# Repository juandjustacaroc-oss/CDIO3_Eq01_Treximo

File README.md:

# CDIO3_Eq01_Treximo: Smart Athletic Timing & Physiological Monitoring System
Sistema distribuido basado en ESP32 para cronometraje automático y monitoreo fisiológico en pruebas de atletismo (100 m), diseñado para proporcionar mediciones precisas de tiempo, velocidad y frecuencia cardíaca en tiempo real. Este proyecto integra comunicación inalámbrica de baja latencia, procesamiento embebido y una interfaz web ligera para ofrecer retroalimentación inmediata al entrenador sin depender de infraestructura externa o servicios en la nube.

# Objetivo del Proyecto
Desarrollar un sistema portátil y autónomo capaz de:
- Detectar automáticamente el inicio y finalización de la carrera.
- Calcular el tiempo exacto del recorrido.
- Estimar la velocidad promedio del atleta.
- Monitorear la frecuencia cardíaca durante la carrera y la fase de recuperación.
- Visualizar métricas en pantalla OLED y en una interfaz web básica embebida.
- Reiniciar el sistema de forma segura para múltiples sesiones consecutivas.

# Arquitectura General
- Peon Salida/Peon Llegada.
- Cerebro Cronometro.
- Banda de variables fisiologicas.
La comunicación entre nodos se realiza mediante ESP-NOW.
El nodo central también opera como punto de acceso WiFi para permitir la visualización de datos desde un smartphone o tablet.

# Estado Actual [MAHD](https://docs.google.com/spreadsheets/d/1o7weHOlPSlPQWPbzmIAxRxXA6ihxt1Q-x_elVm5SotQ/edit?usp=sharing) 
- ✅Hardware funcional
- ✅Comunicación estable entre nodos
- ✅Cronometría precisa basada en eventos
- ❌Monitoreo cardíaco integrado
- ✅Interfaz TFT operativa
- ✅Dashboard web ligero en pruebas

# Librerías necesarias

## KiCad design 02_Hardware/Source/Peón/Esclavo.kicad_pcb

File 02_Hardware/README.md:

# Hardware

## Diseño y Arquitectura Física del Sistema

Esta carpeta contiene todos los recursos asociados al desarrollo físico y electrónico del sistema distribuido basado en ESP32.

El hardware está dividido en tres subsistemas principales:

- 🧠 Cronómetro Central
- 📡 Peones (Salida y Llegada)
- ❤️ Banda de Variables Fisiológicas

---

## Estructura de Carpetas

### 📂 Datasheets/
Contiene únicamente hojas técnicas oficiales (PDF) de los componentes utilizados:
- ESP32
- UWB (DW1000 / RYUW122)
- MAX3010x
- RTC
- Pantalla TFT
- Módulos de carga
- Sensores ultrasónicos

Estos documentos fundamentan las decisiones técnicas adoptadas en el diseño.

---

### 📂 Mechanical/
Archivos mecánicos del proyecto:
- STL (impresión 3D)
- DXF (corte láser)
- CAD (modelos completos)

Incluye:
- Carcasa del cronómetro
- Soportes de peones
- Integración de banda fisiológica

---

### 📂 Source/
Archivos editables de diseño electrónico:
- KiCad
- Altium
- Eagle

Contiene:
- Esquemáticos
- PCB
- Layout
- Gerbers (si aplica)

---

## Consideraciones Técnicas

- Alimentación autónoma con sistema de carga y protección.
- Comunicación inalámbrica UWB para medición de distancia.
- ESP-NOW para eventos críticos de cronometraje.
- Diseño modular para mantenimiento y escalabilidad.

---

## Estado

El hardware ha sido auditado y actualizado tras la revisión técnica del diseño inicial.
Las modificaciones están justificadas en la Matriz de Defensa de Diseño (ver carpeta 01_Gestion).

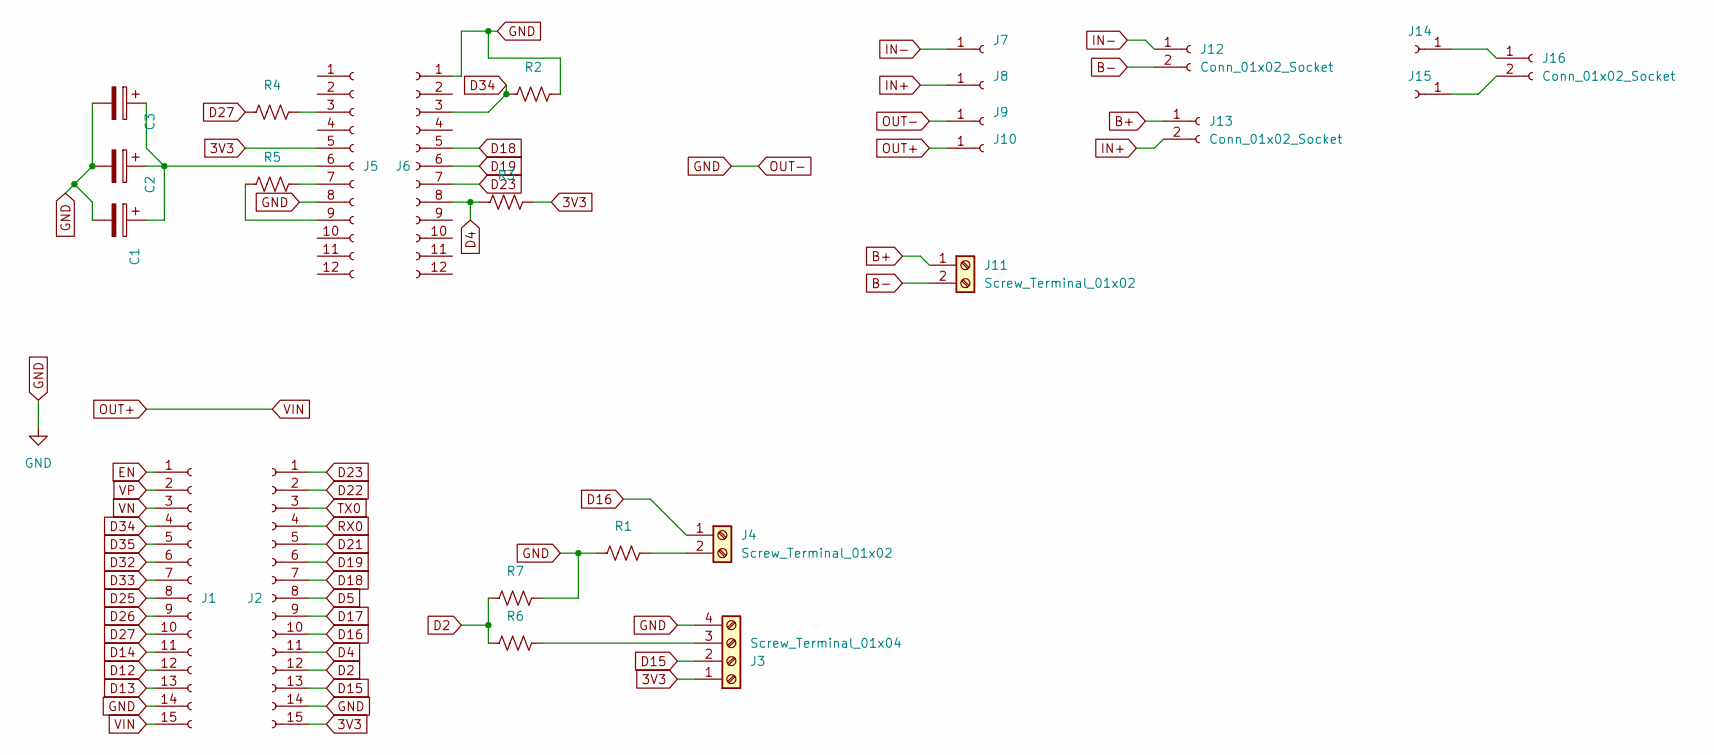
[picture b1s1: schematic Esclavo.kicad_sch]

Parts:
C1, C2, C3: C_Polarized; CP_Radial_D5.0mm_P2.50mm
J1, J2: Conn_01x15_Socket; PinSocket_1x15_P2.54mm_Vertical
J3: Screw_Terminal_01x04; TerminalBlock_Phoenix_MKDS-1,5-4-5.08_1x04_P5.08mm_Horizont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
J4, J11: Screw_Terminal_01x02; TerminalBlock_Phoenix_MKDS-1,5-2-5.08_1x02_P5.08mm_Horizont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
J5, J6: Conn_01x12_Socket; PinSocket_1x12_P2.54mm_Vertical
J7, J8, J9, J10, J14, J15: Conn_01x01_Socket; PinHeader_1x01_P2.54mm_Vertical
J12, J13, J16: Conn_01x02_Socket; PinSocket_1x02_P2.54mm_Vertical
R1, R2, R3, R4, R5, R6, R7: R_US; R_Axial_DIN0207_L6.3mm_D2.5mm_P10.16mm_Horizontal

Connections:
3V3: J2.15, J3.1, J5.5, R3.1
B+: J11.1, J13.1
B-: J11.2, J12.2
D2: J2.12, R6.2, R7.2
D4: J2.11, J6.8, R3.2
D5: J2.8
D12: J1.12
D13: J1.13
D14: J1.11
D15: J2.13, J3.2
D16: J2.10, J4.1
D17: J2.9
D18: J2.7, J6.5
D19: J2.6, J6.6
D21: J2.5
D22: J2.2
D23: J2.1, J6.7
D25: J1.8
D26: J1.9
D27: J1.10, R4.2
D32: J1.6
D33: J1.7
D34: J1.4, J6.3, R2.2
D35: J1.5
EN: J1.1
GND: C1.2, C2.2, C3.2, J1.14, J2.14, J3.4, J5.8, J6.1, J9.1 (Pin_1_1), R1.2, R2.1, R7.1
IN+: J8.1 (Pin_1_1), J13.2
IN-: J7.1 (Pin_1_1), J12.1
unnamed: J3.3, R6.1
unnamed: J4.2, R1.1
unnamed: J5.3, R4.1
unnamed: C1.1, C2.1, C3.1, J5.6
unnamed: J5.7, R5.1
unnamed: J5.9, R5.2
unnamed: J14.1 (Pin_1_1), J16.1
unnamed: J15.1 (Pin_1_1), J16.2
OUT+: J1.15, J10.1 (Pin_1_1)
RX0: J2.4
TX0: J2.3
VN: J1.3
VP: J1.2

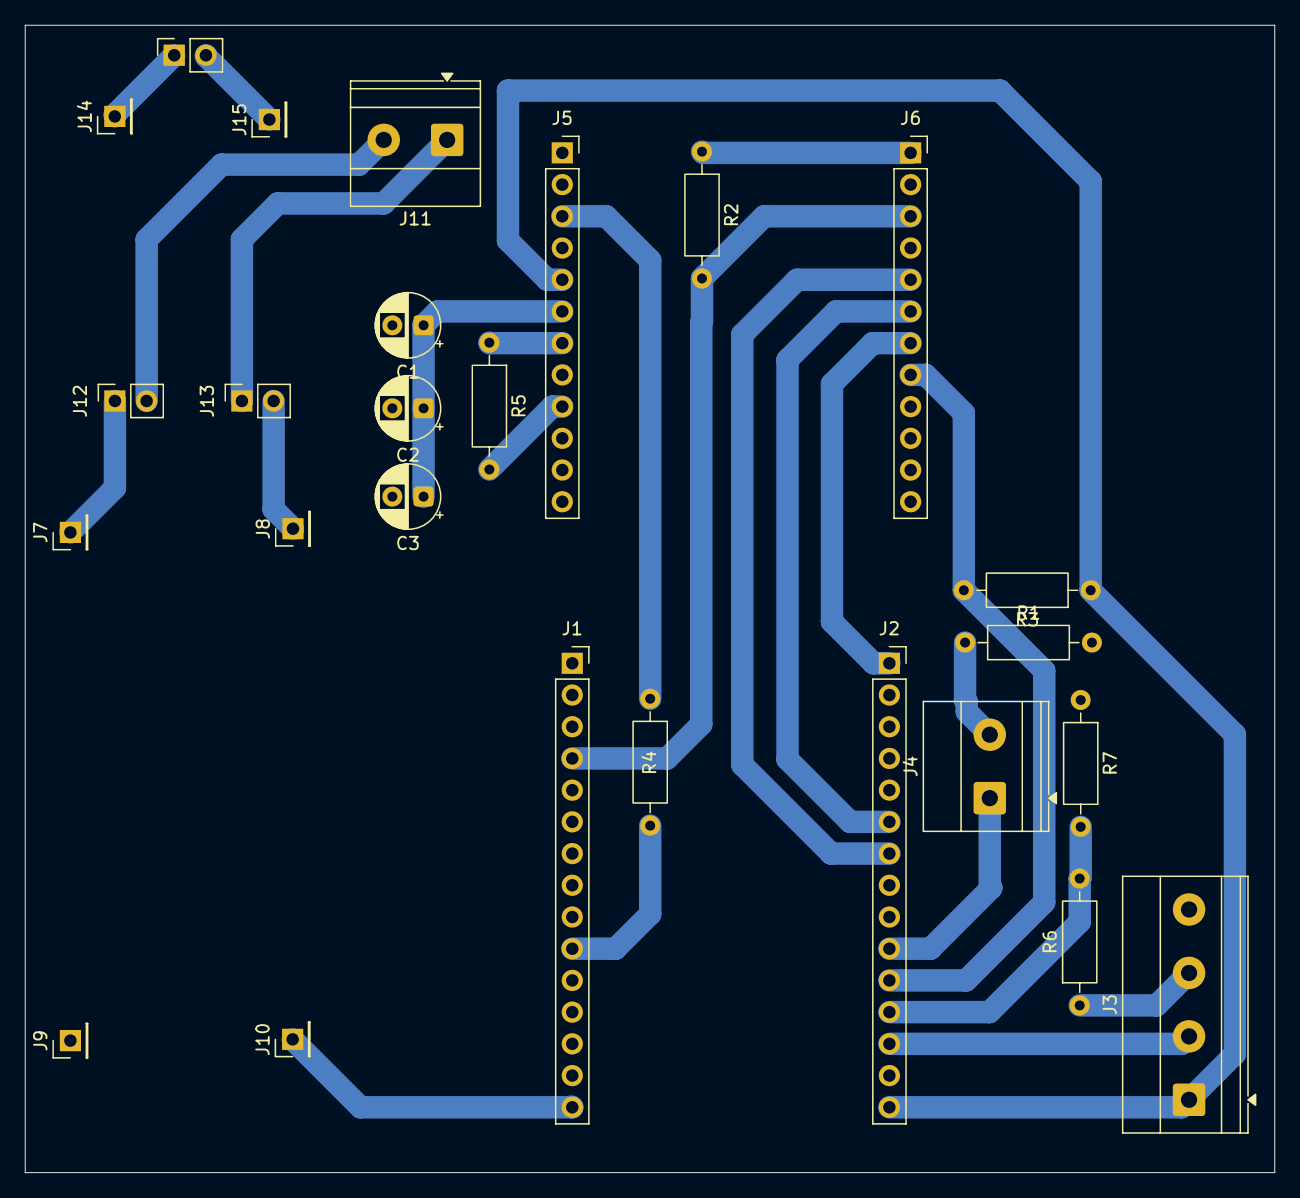
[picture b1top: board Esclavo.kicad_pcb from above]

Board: 2 copper layers, 100.1 x 91.9 mm, 26 parts (0 on the bottom side), 24 nets.

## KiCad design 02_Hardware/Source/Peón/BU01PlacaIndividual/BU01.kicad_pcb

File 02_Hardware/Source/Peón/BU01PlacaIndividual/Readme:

PCB de BU01 para conexión como modulo adicional

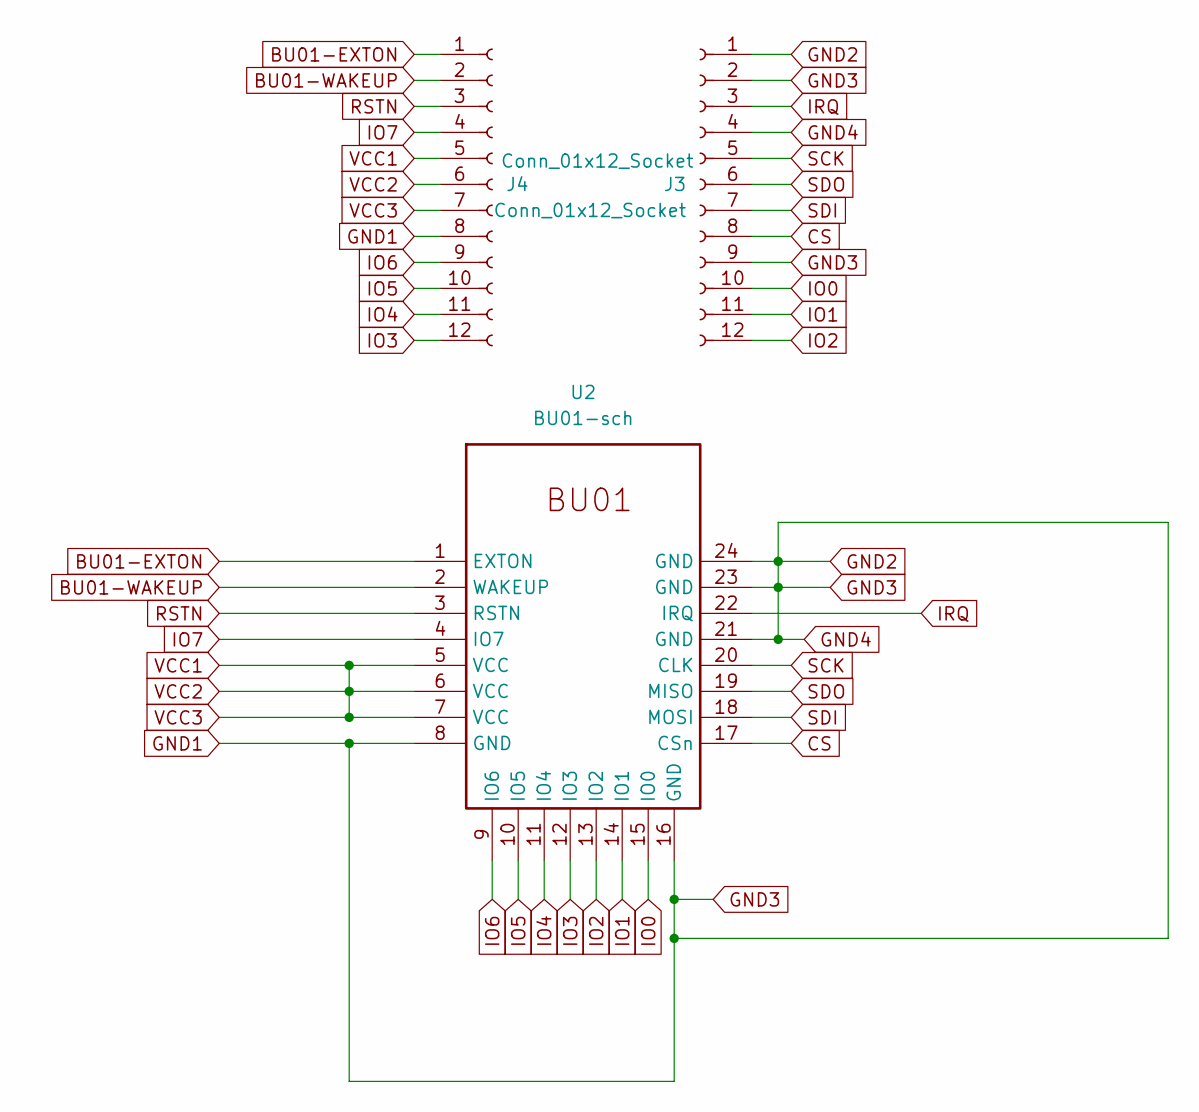
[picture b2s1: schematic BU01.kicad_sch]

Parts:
J3, J4: Conn_01x12_Socket; PinSocket_1x12_P2.54mm_Vertical
U2: BU01-sch; BU01

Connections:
BU01-EXTON: J4.1, U2.1 (EXTON)
BU01-WAKEUP: J4.2, U2.2 (WAKEUP)
CS: J3.8, U2.17 (CSn)
GND1: J3.1, J3.2, J3.4, J3.9, J4.8, U2.8 (GND), U2.16 (GND), U2.21 (GND), U2.23 (GND), U2.24 (GND)
IO0: J3.10, U2.15 (IO0)
IO1: J3.11, U2.14 (IO1)
IO2: J3.12, U2.13 (IO2)
IO3: J4.12, U2.12 (IO3)
IO4: J4.11, U2.11 (IO4)
IO5: J4.10, U2.10 (IO5)
IO6: J4.9, U2.9 (IO6)
IO7: J4.4, U2.4 (IO7)
IRQ: J3.3, U2.22 (IRQ)
RSTN: J4.3, U2.3 (RSTN)
SCK: J3.5, U2.20 (CLK)
SDI: J3.7, U2.18 (MOSI)
SDO: J3.6, U2.19 (MISO)
VCC1: J4.5, J4.6, J4.7, U2.5 (VCC), U2.6 (VCC), U2.7 (VCC)

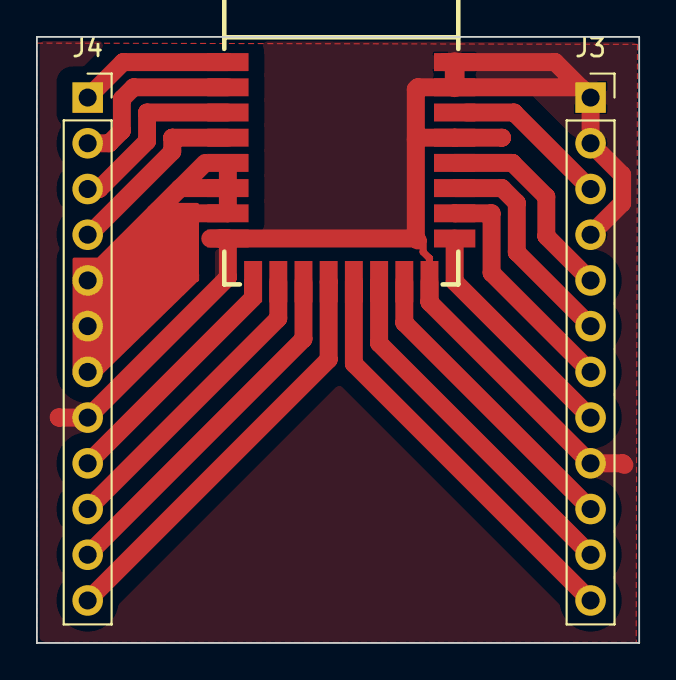
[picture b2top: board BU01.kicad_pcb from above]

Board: 2 copper layers, 33.5 x 33.7 mm, 3 parts (0 on the bottom side), 18 nets.

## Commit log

2026-02-16 README.md
2026-02-16 02_Hardware/Datasheets/.gitkeep
2026-02-16 .gitkeep
2026-02-23 Enhance README with project details and objectives
    Added detailed project description, objectives, architecture, and current status.
2026-02-23 Create BOM
2026-02-23 Código de Cerebro
    A continuación anexo el código de ESP32 para el funcionamiento del cerebro como se planteaba el semestre pasado. Por favor revisar y validar.
2026-02-23 Esquematico de Altium
    Conexiones del semestre pasado realizadas en Altium
2026-02-23 Readme de la gestión del proyecto
    Added detailed documentation for project management, including meeting minutes, BOM, and timelines.
2026-02-23 Enhance README with hardware design details
    Added detailed documentation about the hardware design, architecture, and folder structure for the ESP32-based distributed system.
2026-02-23 Enhance README with firmware and architecture details
    Added detailed documentation about the firmware structure, compilation steps, and software architecture.
2026-02-23 Create Herramientas de Auditoria y Planeación
2026-02-23 Enhance README with project documentation details
    Added detailed sections on documentation, expected content, and project purpose.
2026-02-23 Herramientas de Auditoria y Planeación
2026-02-23 Cronograma de actividades
2026-02-25 Prueba Inicial de la pantalla
    Se hace la primer prueba de la pantalla para el cronómetro y así mostrar que funciona con un código simple
2026-02-25 Alternativa 1 Interfaz del cronómetro
    En este código de arduino se aloja una de las dos alternativas que se va a tener para mostrar los datos en la pantalla del cronómetro
2026-02-26 Segunda Alternativa para cronómetro
    En este código se presenta la segunda alternativa para la interfaz del cronómetro
2026-03-02 Codigo de cronometro basico
    Se tiene una primer visión del cronometro funcional
2026-03-16 Codigo para peones basico
    En este código se aloja el funcionamiento básico del cerebro del sistema al que se quiere llegar
2026-03-16 Código Cerebro con RTC
    Código funcional para el cerebro con un RTC para ver las horas de llegada y salida del atleta
2026-04-12 Revise project status and add libraries section
    Updated project status and added necessary libraries section.
2026-04-13 Rename '01_Gestion' to 'Gestion' in README
2026-04-13 Create Bill Of Materials
2026-04-13 Add Bill Of Materials section to README
    Added Bill Of Materials (BOM) section detailing components for the system, including cost estimates and functions for each item.
2026-04-13 Rename 01_Gestion/Bill Of Materials to 01_Gestion/BOM/Bill Of Materials
2026-04-13 Rename 01_Gestion/Auditoria y Planeación to 01_Gestion/Planeación/Auditoria y Planeación
2026-04-13 Rename 01_Gestion/Cronograma de actividades to 01_Gestion/Planeación/Cronograma de actividades
2026-04-13 Rename PantallaTFT.pdf to LCD_ST7735_TFT.pdf
2026-04-13 TP4056.pdf
2026-04-13 Rename 000194 datasheet TP4056.pdf to TP4056.pdf
2026-04-13 Reloj de tiempo real DS3231
2026-04-13 PushButton
2026-04-13 Rename ts40.pdf to Pushbutton_Mouser.pdf
2026-04-13 Led Rojo
2026-04-13 Rename BIR-BM1331.PDF to LED.PDF
2026-04-13 Rename test_Ultrasonido1.ino to test_Ultrasonido1.ino
2026-04-13 Rename 03_Firmware/Src/test_Ultrasonido1.ino to 03_Firmware/Src/PruebaIndividual/test_Ultrasonido2.ino
2026-04-13 Rename Test_PantallaTFT1.ino to Test_PantallaTFT1.ino
2026-04-13 Add description for individual test codes folder
2026-04-13 Rename '03_Firmware' to 'Firmware' in README
2026-04-13 Document project tasks and acceptance criteria
    Added detailed project tasks with purposes, activities, acceptance criteria, and evidence for each item.
2026-04-13 Create IPAC
2026-04-13 Auditoria.gitkeep
2026-04-14 Auditoria.md
2026-04-25 Add README for BU01 PCB module
2026-04-26 Implement KY-039 pulse sensor functionality
    Refactor code to implement KY-039 pulse sensor functionality, including reading analog values, detecting pulses, and calculating BPM. Removed ultrasonic sensor code and added necessary configurations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
2026-04-26 Create MAX30102
2026-04-26 Add Test_KY039.ino file
2026-04-26 Add Test_MAX30102 file for MAX30102 testing
2026-04-26 Rename Test_MAX30102 to Test_MAX30102.ino
2026-04-27 PCB del eslabon básico
    En este .zip está alojada la primer versión del diseño de PCB para la implementación básica de los eslabones, es decir, el sistema que está compuesto por ESP32, un led y el ultrasonido; faltando la i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
2026-05-02 Add files via upload
    TAG UWB
2026-05-02 Rename UWB.ino to TEST_UWB_TAG.ino
2026-05-02 Add TEST_UWB_ANCHOR.ino file
2026-05-02 Rename UWB_SPI_TEST.ino to TEST_UWB_SPI.ino
2026-05-02 Rename TEST_UWB_ANCHOR.ino to Test_UWB_ANCHOR.ino
2026-05-02 Rename TEST_UWB_SPI.ino to Test_UWB_SPI.ino
2026-05-02 Rename TEST_UWB_TAG.ino to Test_UWB_TAG.ino
2026-05-02 Fix UWB link formatting in README.md
    Updated UWB link formatting in README.
2026-05-02 Add Peón de Llegada functionality for distance sensing
    This file implements the Peón de Llegada functionality for an ESP32 device using HC-SR04 and ESP-NOW to send distance measurements.
2026-05-02 Change LED GPIO pin from 18 to 4
2026-05-02 Código actualizado del peón de salida básico
2026-05-03 Refactor UWB TAG initialization and address handling
2026-05-03 Update and rename CodigoPeonSalida.ino to PeonSalidaV1
2026-05-03 Rename PeonSalidaV1 to Peon_SalidaV1
2026-05-03 Rename Peon_SalidaV1 to Peon_SalidaV1.ino
2026-05-03 Rename Peon_LlegadaV1 to Peon_LlegadaV1.ino
2026-05-03 Change LED_PIN definition from 18 to 4
2026-05-03 Rename Test_UWB_ANCHOR.ino to Test_UWB_ANCHOR_V1.ino
2026-05-03 Rename Test_UWB_TAG.ino to Test_UWB_TAG_V1.ino
2026-05-03 Add Test_UWB_ANCHOR_V2.ino file
    Cambio de ShortRange a LongRange en los UWB
2026-05-03 Implement optimized DW1000 TAG features
    Optimización de código DW1000 para mayor distancia de lectura
2026-05-04 Update TFT interface status to operational
2026-05-04 Create Expediente Técnico
2026-05-04 Update Expediente Técnico
2026-05-04 Informe de Avance Técnico
2026-05-06 Create Test2_MAX30102
2026-05-06 Rename Test2_MAX30102 to Test2_MAX30102.ino
2026-05-11 Archivos de esquemático y PCB para el eslabón completo
    Se encuentra alojado el archivo gerber de salida para poder hacer la impresión de la placa, a demás se recomienda hacerle espejo ya que hace parte de la capa bottom cupper
2026-05-13 Create AlternativaPantalla3.0.ino
    Código para visualización de distancia en la TFT
2026-05-13 Create CodigoFinalPantalla.ino
    Este es el código final para la interfaz física del cronómetro para visualización de las variables tales como tiempo, frecuencia cardiaca, velocidad y distancia
2026-05-14 Archivos STL de peón y Cronometro
    Estos son los archivos para la impresión 3D iniciales.
2026-05-14 Código de peones salida y llegada
    Códigos con transmisión adecuada al cerebro. Es posible añadir correcciones en activación del led
2026-05-15 Add initial Flutter e interfaz section to README
2026-05-15 Súbida de todo el sistema en flutter y android studio
    En este commit se sube todo el sistema de la interfaz con funcionamiento simulado y sin conexión a los datos del ESP32
2026-05-15 Recuperación Versión Antigua
2026-05-15 Eliminación Archivo de proyecto no relevante
2026-05-16 Versión corregida de archivos 3D
    Se realizaron algunas cejitas para ubicar los pulsadores, se cambió la ubicación de los puertos de carga de los peones para que queden a la altura de las baterías, se corrigió el orificio de las bate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
2026-05-18 Cambiar ubicación
    Alternativas de pantalla pasan a pruebas individuales, Cronometros básicos pasan a pruebas individuales
2026-05-18 Ultima versión
    Se añade el cerebro (Cronometro) y peón de llegada y se descarta la banda momentaneamente
2026-05-20 Add new firmware version for Cerebro Treximo
2026-05-20 Reorganización de carpetas
2026-05-20 Add Peon_Llegada_AnchorUWB_v3.7.ino file
2026-05-20 Expediente Técnico
